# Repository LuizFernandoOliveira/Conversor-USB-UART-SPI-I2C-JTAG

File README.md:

# Conversor-USB-UART-SPI-I2C-JTAG

## Descrição
Esta PCB trata-se de um poderoso circuito eletrônico que transforma uma única porta USB em múltiplos canais seriais de alta velocidade, ideal para desenvolvedores que precisam de versatilidade em seus projetos.

---

## Descrições técnicas

- Interface USB: Dispositivo USB High-Speed de 480Mbps;
- Possui duas UART (UART0 e UART1), uma SPI, uma I2C, uma JTAG e 8 pinos de GPIOs controlados diretamente pela USB;
- Taxa de Transmissão (Baud Rate): Variável de 1200bps até 6Mbps;
- Alimentação Principal: Requer apenas 3.3V;
- Controle de Fluxo: Suporte completo a Hardware Flow Control (CTS e RTS);
- Buffering (FIFO):
  - RX FIFO: 2048 bytes por UART.
  - TX FIFO: 1024 bytes por UART.
- Configurações UART:
  - Bits de Dados: 8 bits;
  - Paridade: Ímpar, Par e Nenhuma;
  - Bits de Parada: 1 ou 2.

---

## Estrutura do repositório
Os arquivos de hardware foram desenvolvidos utilizando o KiCad 9.0.
- **`.kicad_pcb`**: Layout da placa de circuito impresso (Board).
- **`.kicad_sch`**: Esquemático eletrônico do sistema (Schematic).
- **`.kicad_pro`**: Gerenciador de projeto do KiCad (Project).

---

## Autor
**Dr. Luiz Fernando Pinto de Oliveira**

*Engenheiro Eletrônico especializado em Sistemas Embarcados e Ultra-Low Power.*
- **Website:** [FAPLO](https://faplo.webnode.page/)
- **LinkedIn:** [lfpo](https://www.linkedin.com/in/lfpo/)

---

Shield: [![CC BY-NC-ND 4.0][cc-by-nc-nd-shield]][cc-by-nc-nd]

This work is licensed under a
[Creative Commons Attribution-NonCommercial-NoDerivs 4.0 International License][cc-by-nc-nd].

[![CC BY-NC-ND 4.0][cc-by-nc-nd-image]][cc-by-nc-nd]

[cc-by-nc-nd]: http://creativecommons.org/licenses/by-nc-nd/4.0/
[cc-by-nc-nd-image]: https://licensebuttons.net/l/by-nc-nd/4.0/88x31.png
[cc-by-nc-nd-shield]: https://img.shields.io/badge/License-CC%20BY--NC--ND%204.0-lightgrey.svg

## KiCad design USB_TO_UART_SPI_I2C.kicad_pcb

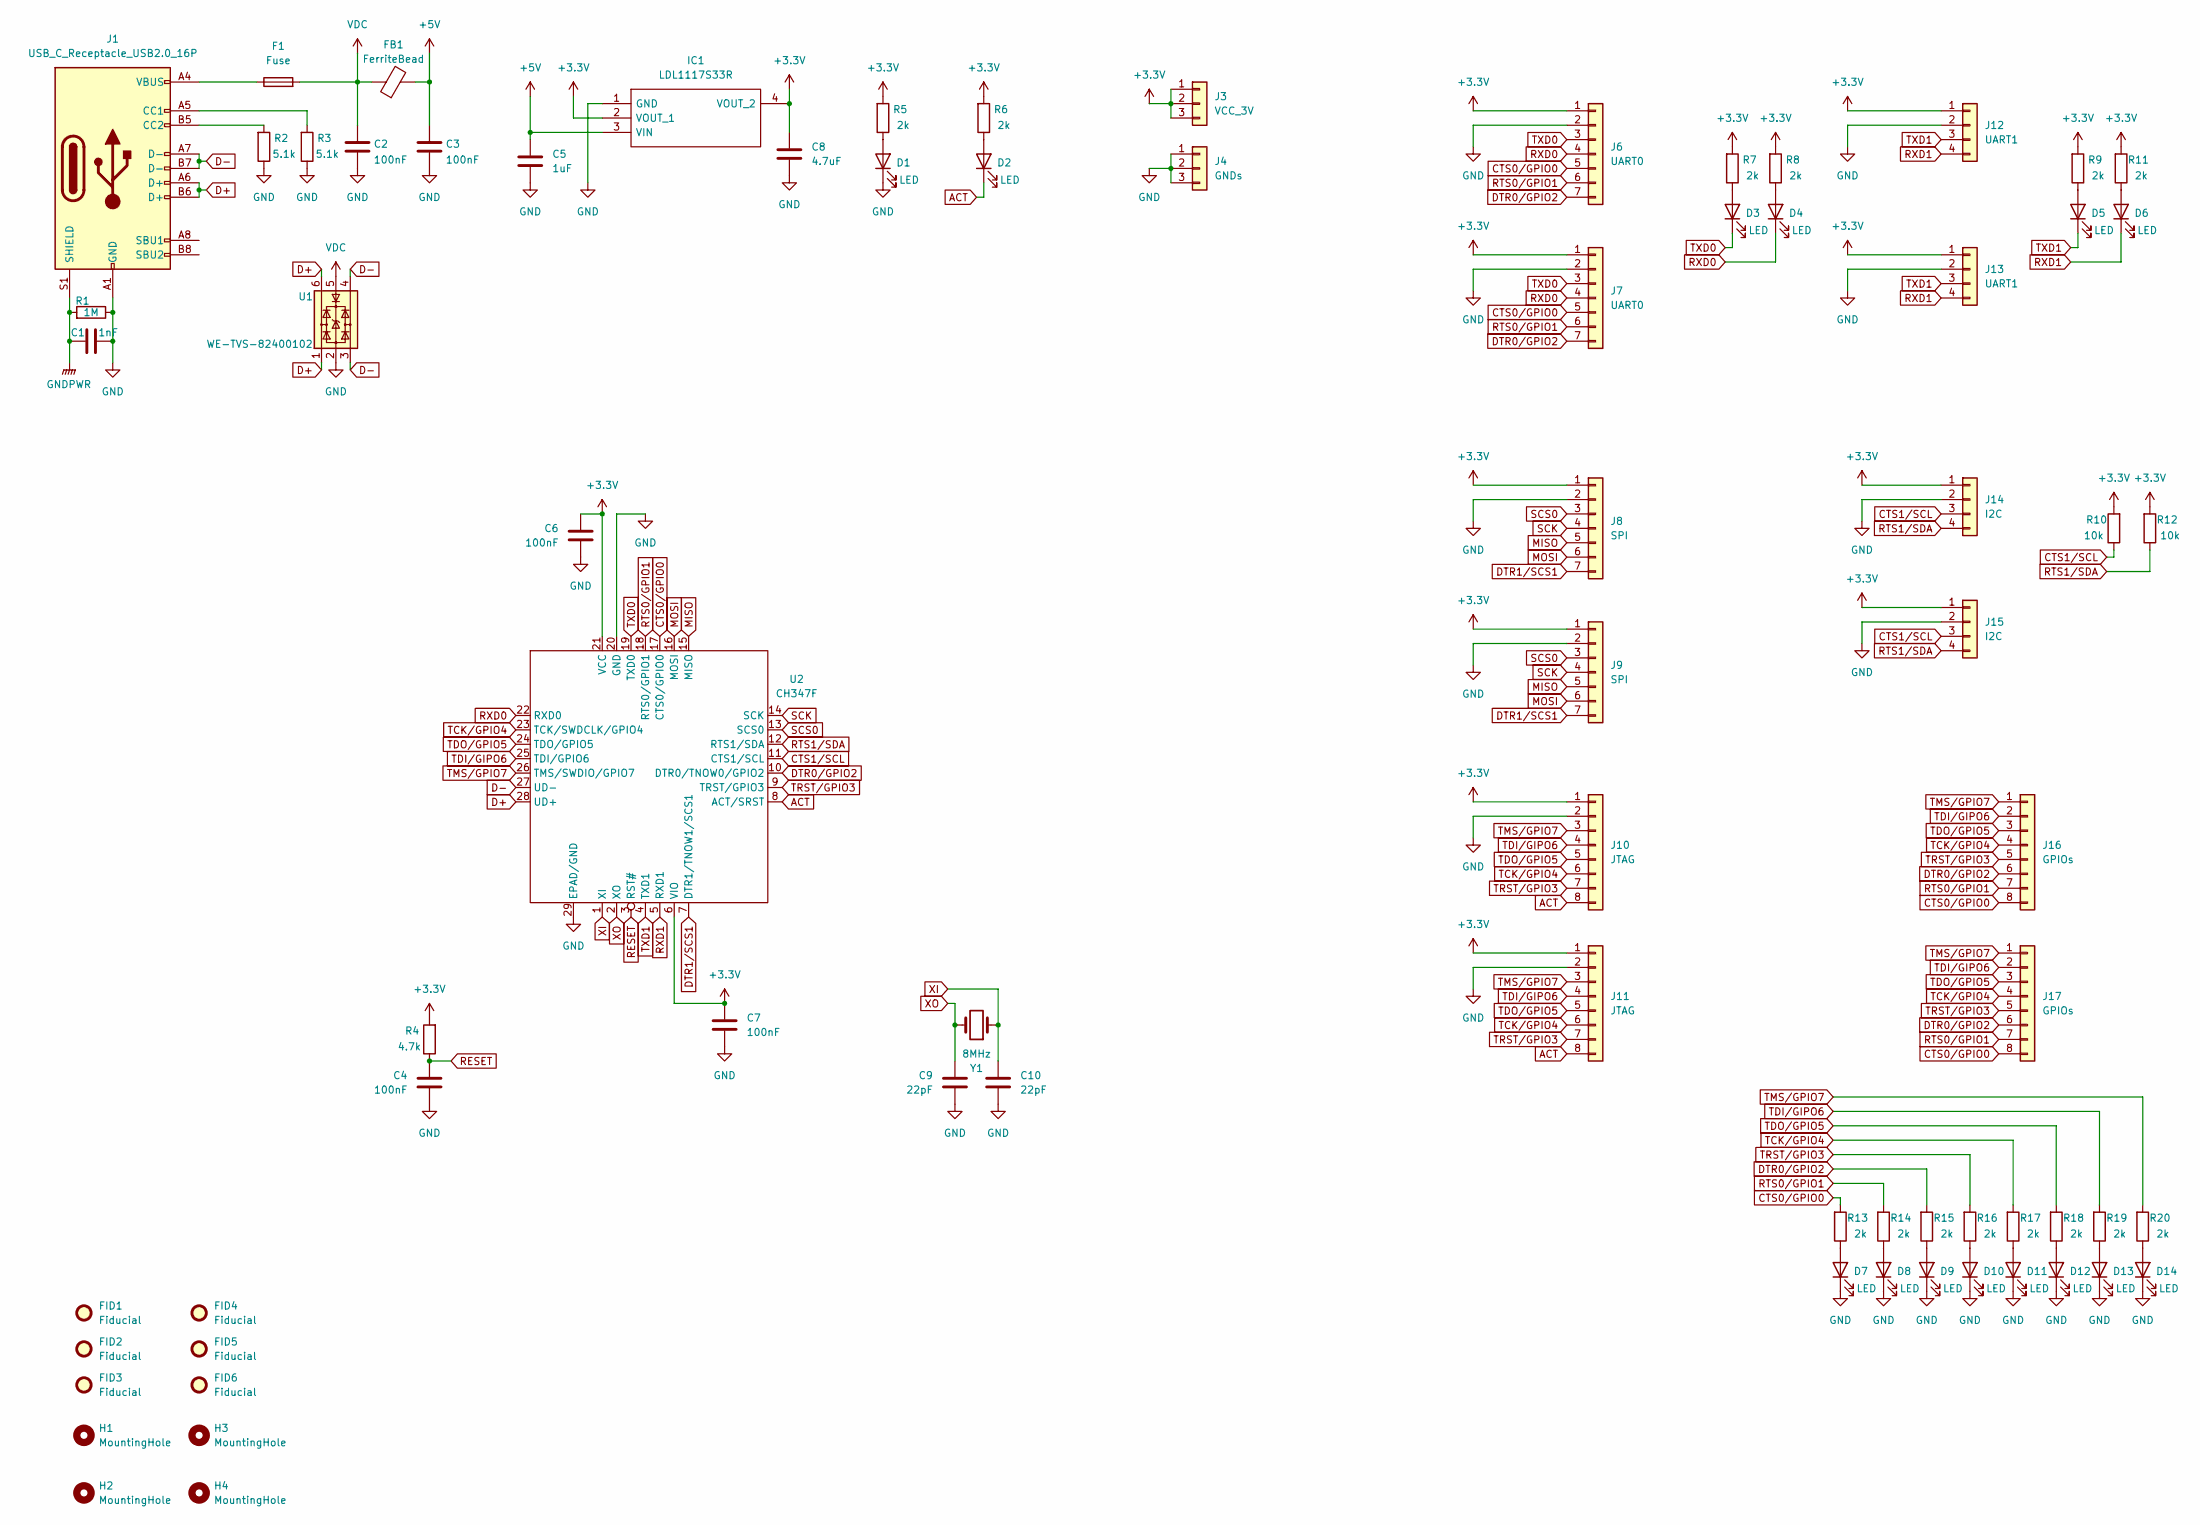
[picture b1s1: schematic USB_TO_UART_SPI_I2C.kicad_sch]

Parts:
C1: 1nF; C_0805_2012Metric
C2, C3, C4, C6, C7: 100nF; C_0805_2012Metric
C5: 1uF; C_0805_2012Metric
C8: 4.7uF; C_0805_2012Metric
C9, C10: 22pF; C_0805_2012Metric
D1, D2, D3, D4, D5, D6, D7, D8, D9, D10, D11, D12, D13, D14: LED; LED_0805_2012Metric
F1: Fuse; Fuse_0805_2012Metric
FB1: FerriteBead; L_0805_2012Metric
FID1, FID2, FID3, FID4, FID5, FID6: Fiducial; Fiducial_1mm_Mask2mm
H1, H2, H3, H4: MountingHole; MountingHole_3.2mm_M3_DIN965
IC1: LDL1117S33R; SOT230P700X180-4N; Manufacturer_Part_Number LDL1117S33R; Mouser Part Number 511-LDL1117S33R
J1: USB_C_Receptacle_USB2.0_16P; USB_C_Receptacle_HRO_TYPE-C-31-M-12
J3: VCC_3V; PinHeader_1x03_P2.54mm_Vertical
J4: GNDs; PinHeader_1x03_P2.54mm_Vertical
J6: UART0; PinHeader_1x07_P2.54mm_Vertical
J7: UART0; JST_XH_S7B-XH-A_1x07_P2.50mm_Horizontal
J8: SPI; PinHeader_1x07_P2.54mm_Vertical
J9: SPI; JST_XH_S7B-XH-A_1x07_P2.50mm_Horizontal
J10: JTAG; PinHeader_1x08_P2.54mm_Vertical
J11: JTAG; JST_XH_S8B-XH-A-1_1x08_P2.50mm_Horizontal
J12: UART1; PinHeader_1x04_P2.54mm_Vertical
J13: UART1; JST_XH_S4B-XH-A_1x04_P2.50mm_Horizontal
J14: I2C; PinHeader_1x04_P2.54mm_Vertical
J15: I2C; JST_XH_S4B-XH-A_1x04_P2.50mm_Horizontal
J16: GPIOs; PinHeader_1x08_P2.54mm_Vertical
J17: GPIOs; JST_XH_S8B-XH-A-1_1x08_P2.50mm_Horizontal
R1: 1M; R_0805_2012Metric
R2, R3: 5.1k; R_0805_2012Metric
R4: 4.7k; R_0805_2012Metric
R5, R6, R7, R8, R9, R11, R13, R14, R15, R16, R17, R18, R19, R20: 2k; R_0805_2012Metric
R10, R12: 10k; R_0805_2012Metric
U1: WE-TVS-82400102; SOT-23-6
U2: CH347F
Y1: 8MHz; Crystal_SMD_3225-4Pin_3.2x2.5mm

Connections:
+3.3V: C6.1, C7.1, C8.1, IC1.2 (VOUT_1), IC1.4 (VOUT_2), J3.1, J3.2, J3.3, J6.1, J7.1, J8.1, J9.1, J10.1, J11.1, J12.1, J13.1, J14.1, J15.1, R4.2, R5.2, R6.2, R7.2, R8.2, R9.2, R10.2, R11.2, R12.2, U2.6 (VIO), U2.21 (VCC)
+5V: C3.1, C5.1, FB1.2, IC1.3 (VIN)
ACT: D2.1 (K), J10.8, J11.8, U2.8 (ACT/SRST)
CTS0/GPIO0: J6.5, J7.5, J16.8, J17.8, R13.2, U2.17 (CTS0/GPIO0)
CTS1/SCL: J14.3, J15.3, R10.1, U2.11 (CTS1/SCL)
D+: J1.A6 (D+), J1.B6 (D+), U1.1, U1.6, U2.28 (UD+)
D-: J1.A7 (D-), J1.B7 (D-), U1.3, U1.4, U2.27 (UD-)
DTR0/GPIO2: J6.7, J7.7, J16.6, J17.6, R15.2, U2.10 (DTR0/TNOW0/GPIO2)
DTR1/SCS1: J8.7, J9.7, U2.7 (DTR1/TNOW1/SCS1)
GND: C1.2, C2.2, C3.2, C4.2, C5.2, C6.2, C7.2, C8.2, C9.2, C10.2, D1.1 (K), D7.1 (K), D8.1 (K), D9.1 (K), D10.1 (K), D11.1 (K), D12.1 (K), D13.1 (K), D14.1 (K), IC1.1 (GND), J1.A1 (GND), J1.A12 (GND), J1.B1 (GND), J1.B12 (GND), J4.1, J4.2, J4.3, J6.2, J7.2, J8.2, J9.2, J10.2, J11.2, J12.2, J13.2, J14.2, J15.2, R1.1, R2.1, R3.1, U1.2, U2.20 (GND), U2.29 (EPAD/GND)
GNDPWR: C1.1, J1.S1 (SHIELD), R1.2
MISO: J8.5, J9.5, U2.15 (MISO)
MOSI: J8.6, J9.6, U2.16 (MOSI)
unnamed: D1.2 (A), R5.1
unnamed: D2.2 (A), R6.1
unnamed: D3.2 (A), R7.1
unnamed: D4.2 (A), R8.1
unnamed: D5.2 (A), R9.1
unnamed: D6.2 (A), R11.1
unnamed: D7.2 (A), R13.1
unnamed: D8.2 (A), R14.1
unnamed: D9.2 (A), R15.1
unnamed: D10.2 (A), R16.1
unnamed: D11.2 (A), R17.1
unnamed: D12.2 (A), R18.1
unnamed: D13.2 (A), R19.1
unnamed: D14.2 (A), R20.1
unnamed: F1.1, J1.A4 (VBUS), J1.A9 (VBUS), J1.B4 (VBUS), J1.B9 (VBUS)
unnamed: J1.A5 (CC1), R3.2
unnamed: J1.B5 (CC2), R2.2
RESET: C4.1, R4.1, U2.3 (RST#)
RTS0/GPIO1: J6.6, J7.6, J16.7, J17.7, R14.2, U2.18 (RTS0/GPIO1)
RTS1/SDA: J14.4, J15.4, R12.1, U2.12 (RTS1/SDA)
RXD0: D4.1 (K), J6.4, J7.4, U2.22 (RXD0)
RXD1: D6.1 (K), J12.4, J13.4, U2.5 (RXD1)
SCK: J8.4, J9.4, U2.14 (SCK)
SCS0: J8.3, J9.3, U2.13 (SCS0)
TCK/GPIO4: J10.6, J11.6, J16.4, J17.4, R17.2, U2.23 (TCK/SWDCLK/GPIO4)
TDI/GIPO6: J10.4, J11.4, J16.2, J17.2, R19.2, U2.25 (TDI/GPIO6)
TDO/GPIO5: J10.5, J11.5, J16.3, J17.3, R18.2, U2.24 (TDO/GPIO5)
TMS/GPIO7: J10.3, J11.3, J16.1, J17.1, R20.2, U2.26 (TMS/SWDIO/GPIO7)
TRST/GPIO3: J10.7, J11.7, J16.5, J17.5, R16.2, U2.9 (TRST/GPIO3)
TXD0: D3.1 (K), J6.3, J7.3, U2.19 (TXD0)
TXD1: D5.1 (K), J12.3, J13.3, U2.4 (TXD1)
VDC: C2.1, F1.2, FB1.1, U1.5
XI: C10.1, U2.1 (XI), Y1.1
XO: C9.1, U2.2 (XO), Y1.2

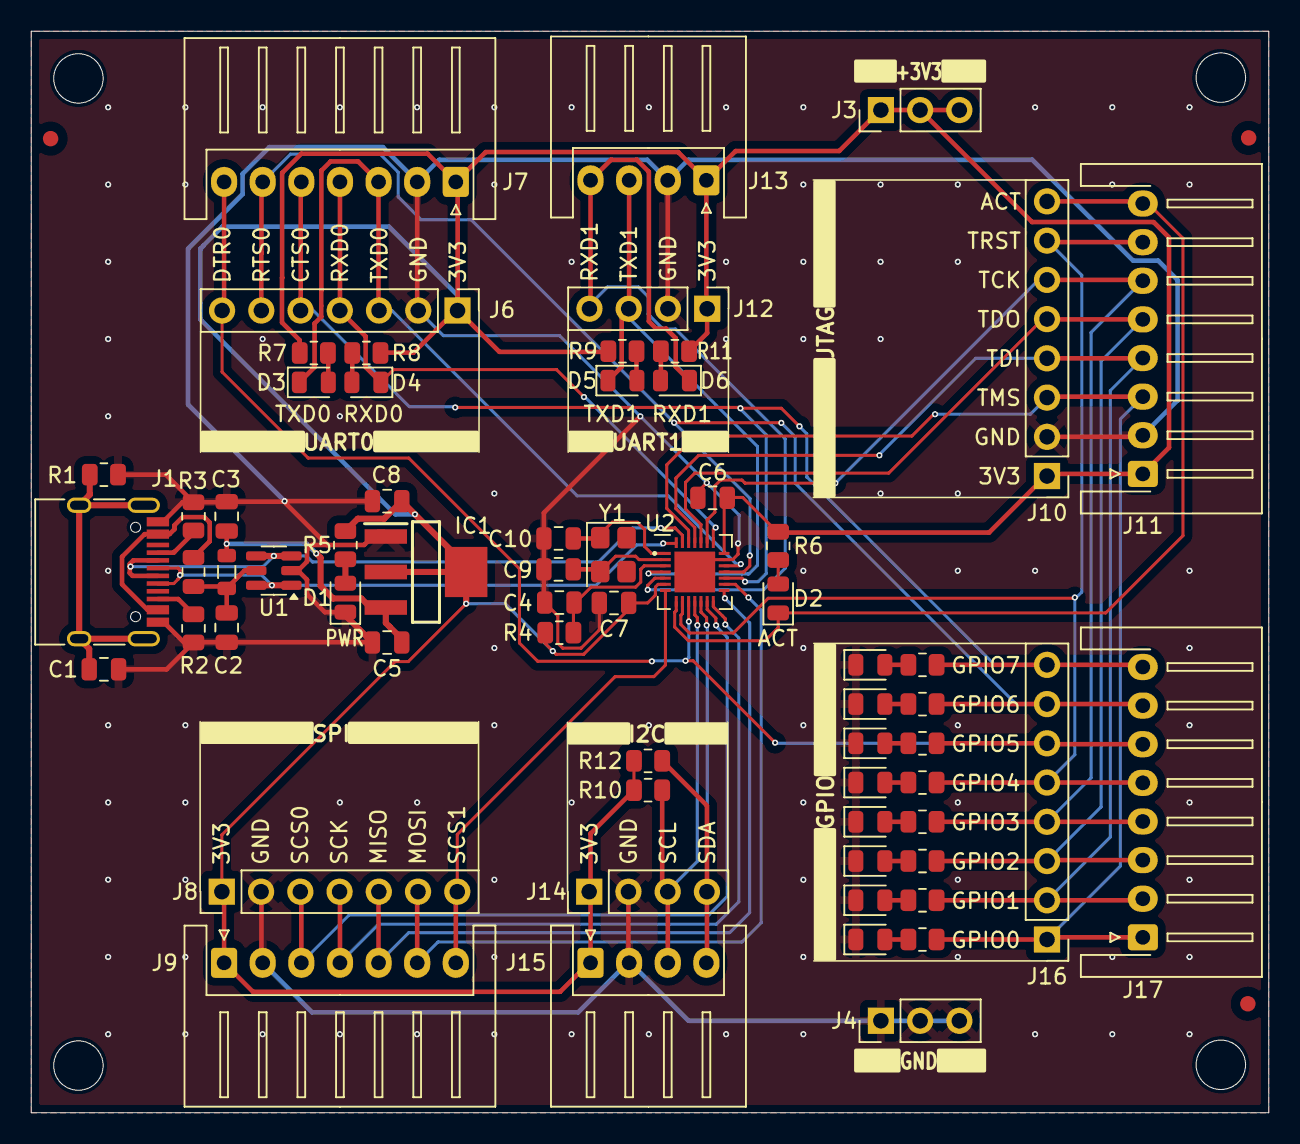
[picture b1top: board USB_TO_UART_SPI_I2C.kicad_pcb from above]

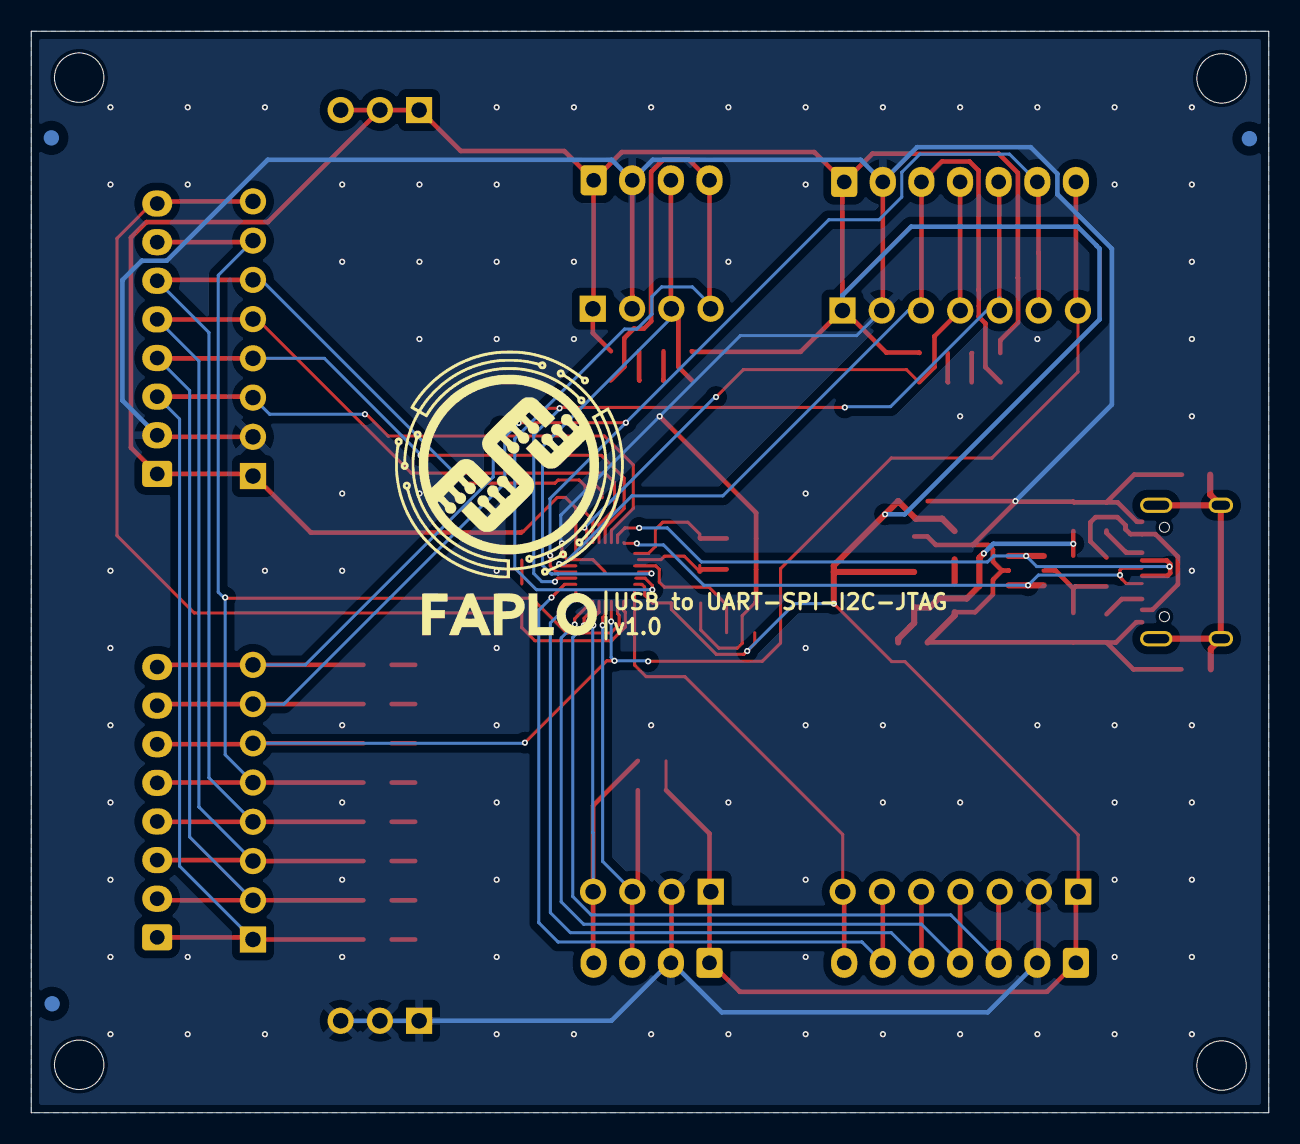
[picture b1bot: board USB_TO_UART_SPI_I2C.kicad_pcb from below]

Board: 2 copper layers, 80.1 x 70.0 mm, 75 parts (3 on the bottom side), 47 nets.

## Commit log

2026-04-17 Inicialização do repositório
2026-04-17 Enhance README with project details and author info
    Added project status badges, technical descriptions, repository structure, and author information to README.
2026-04-17 Add LICENSE file with Creative Commons license
    Added Creative Commons Attribution-NonCommercial-NoDerivatives 4.0 International Public License to the project.
